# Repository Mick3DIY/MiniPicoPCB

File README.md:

<picture>
    
</picture>

# MiniPicoPCB

A simple PCB for the Raspberry Pi Pico with screw terminal headers (GPIOs, +3.3V, GND) to experiment with students.

## Printed Circuit Board (PCB) :

As part of an educational project, the schematic and PCB are made with [KiCad](https://www.kicad.org) version 9 ([kicad](kicad/) folder).

:bulb: All important parameters are stored in the schematic/PCB editors **text variables** (common project variables).

## Schematic :

## Printed Circuit Board (PCB) :

## PCB 3D view :

Thanks to [AISLER](https://aisler.net) PCB manufacturer :eu:

Get a unique 10€ coupon code in <ins>your first order</ins> in [AISLER](https://aisler.net) with my referral code : `MakeInEurope-ECYPW` :heart:

Thanks to "Jimmi Henry" for his 3D libraries (including this PCB Terminal Blocks)  in [GRABCAD Community](https://grabcad.com/jimmi.henry-1) in the [kicad/imports](kicad/imports) folder. 

## Bill Of Materials (BOM) :

| Ref  | Qty | Value | Footprint | Description |
| :---: | :---: | :--- | :--- | :--- |
| J1 ⟶ J10  | 10  | Screw_Terminal_01x05 | TerminalBlock_TE-Connectivity:TerminalBlock_TE_282834-5_1x05_P2.54mm_Horizontal | ... |
| J11, J12  | 2  | Conn_01x20_Socket | Connector_PinSocket_2.54mm:PinSocket_1x20_P2.54mm_Vertical | ... |

## TODO :

- [x] Add PDF files for the schematic and PCB
- [x] Add KiCad step file for the enclosure
- [ ] Add more files and examples, any ideas ? :laughing:

## Documentation :

Raspberry Pi Pico : https://www.raspberrypi.com/products/raspberry-pi-pico/

TE PCB terminal blocks : https://www.te.com/en/product-282834-5.html

> [!NOTE]
> Big thanks to the [KiCad](https://www.kicad.org) and plugins communities. :heart:

Happy soldering, coding & have fun ! :partying_face:

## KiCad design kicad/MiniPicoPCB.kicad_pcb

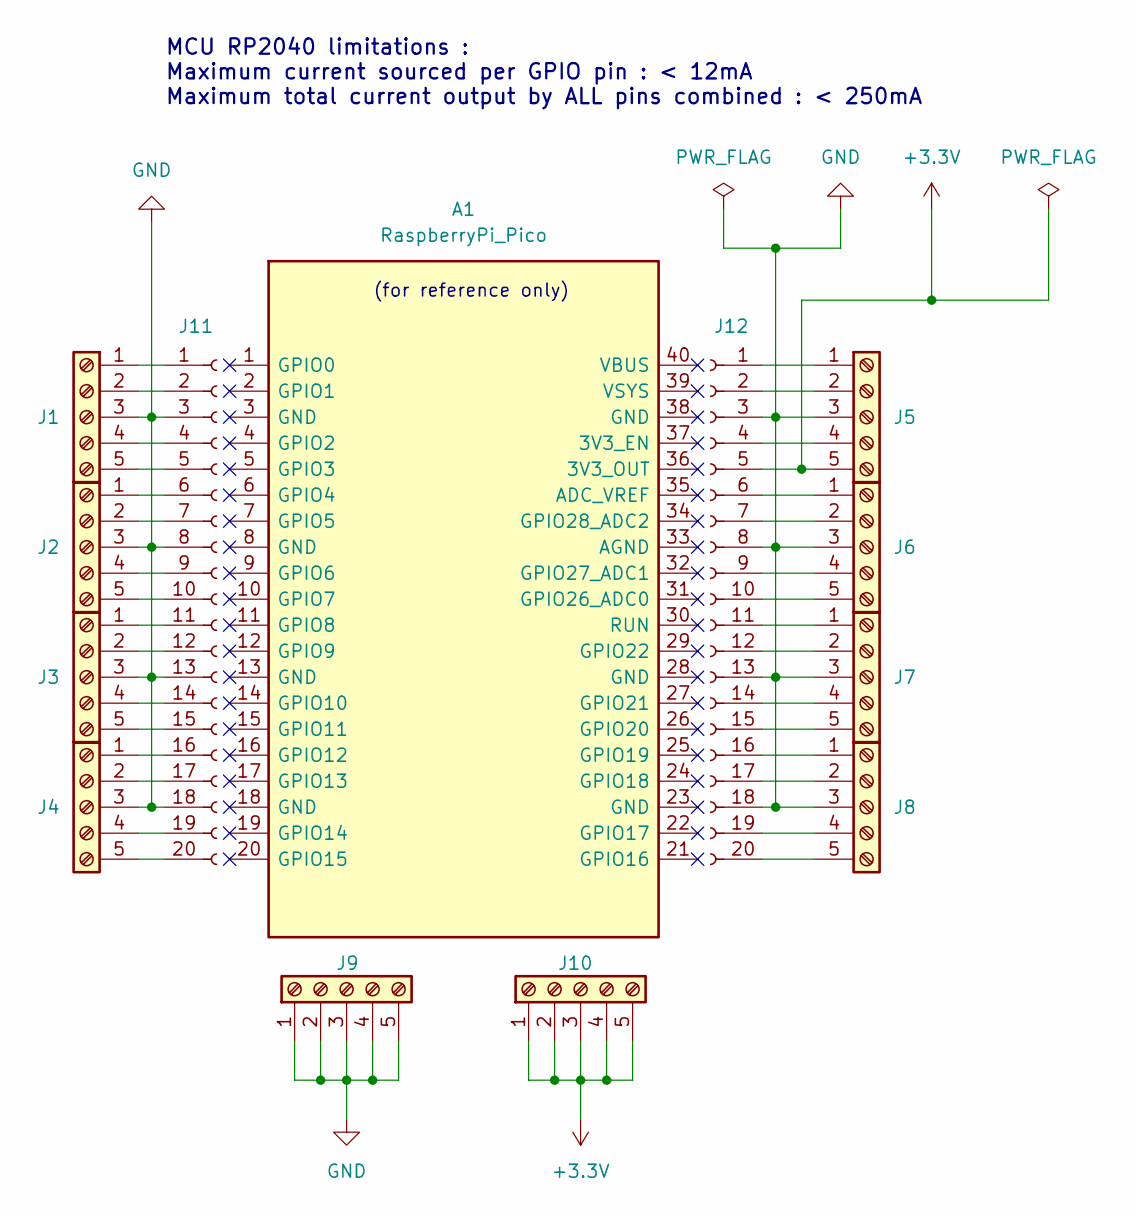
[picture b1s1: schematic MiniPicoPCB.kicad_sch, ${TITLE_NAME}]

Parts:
A1: RaspberryPi_Pico; RaspberryPi_Pico_Common_Unspecified
J1, J2, J3, J4, J5, J6, J7, J8, J9, J10: Screw_Terminal_01x05; TerminalBlock_TE_282834-5_1x05_P2.54mm_Horizontal
J11, J12: Conn_01x20_Socket; PinSocket_1x20_P2.54mm_Vertical

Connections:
+3.3V: J5.5, J10.1, J10.2, J10.3, J10.4, J10.5, J12.5
GND: J1.3, J2.3, J3.3, J4.3, J5.3, J6.3, J7.3, J8.3, J9.1, J9.2, J9.3, J9.4, J9.5, J11.3, J11.8, J11.13, J11.18, J12.3, J12.8, J12.13, J12.18
unnamed: J1.1, J11.1
unnamed: J1.2, J11.2
unnamed: J1.4, J11.4
unnamed: J1.5, J11.5
unnamed: J2.1, J11.6
unnamed: J2.2, J11.7
unnamed: J2.4, J11.9
unnamed: J2.5, J11.10
unnamed: J3.1, J11.11
unnamed: J3.2, J11.12
unnamed: J3.4, J11.14
unnamed: J3.5, J11.15
unnamed: J4.1, J11.16
unnamed: J4.2, J11.17
unnamed: J4.4, J11.19
unnamed: J4.5, J11.20
unnamed: J5.1, J12.1
unnamed: J5.2, J12.2
unnamed: J5.4, J12.4
unnamed: J6.1, J12.6
unnamed: J6.2, J12.7
unnamed: J6.4, J12.9
unnamed: J6.5, J12.10
unnamed: J7.1, J12.11
unnamed: J7.2, J12.12
unnamed: J7.4, J12.14
unnamed: J7.5, J12.15
unnamed: J8.1, J12.16
unnamed: J8.2, J12.17
unnamed: J8.4, J12.19
unnamed: J8.5, J12.20

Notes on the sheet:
MCU RP2040 limitations : Maximum current sourced per GPIO pin : < 12mA Maximum total current output by ALL pins combined : < 250mA
(for reference only)

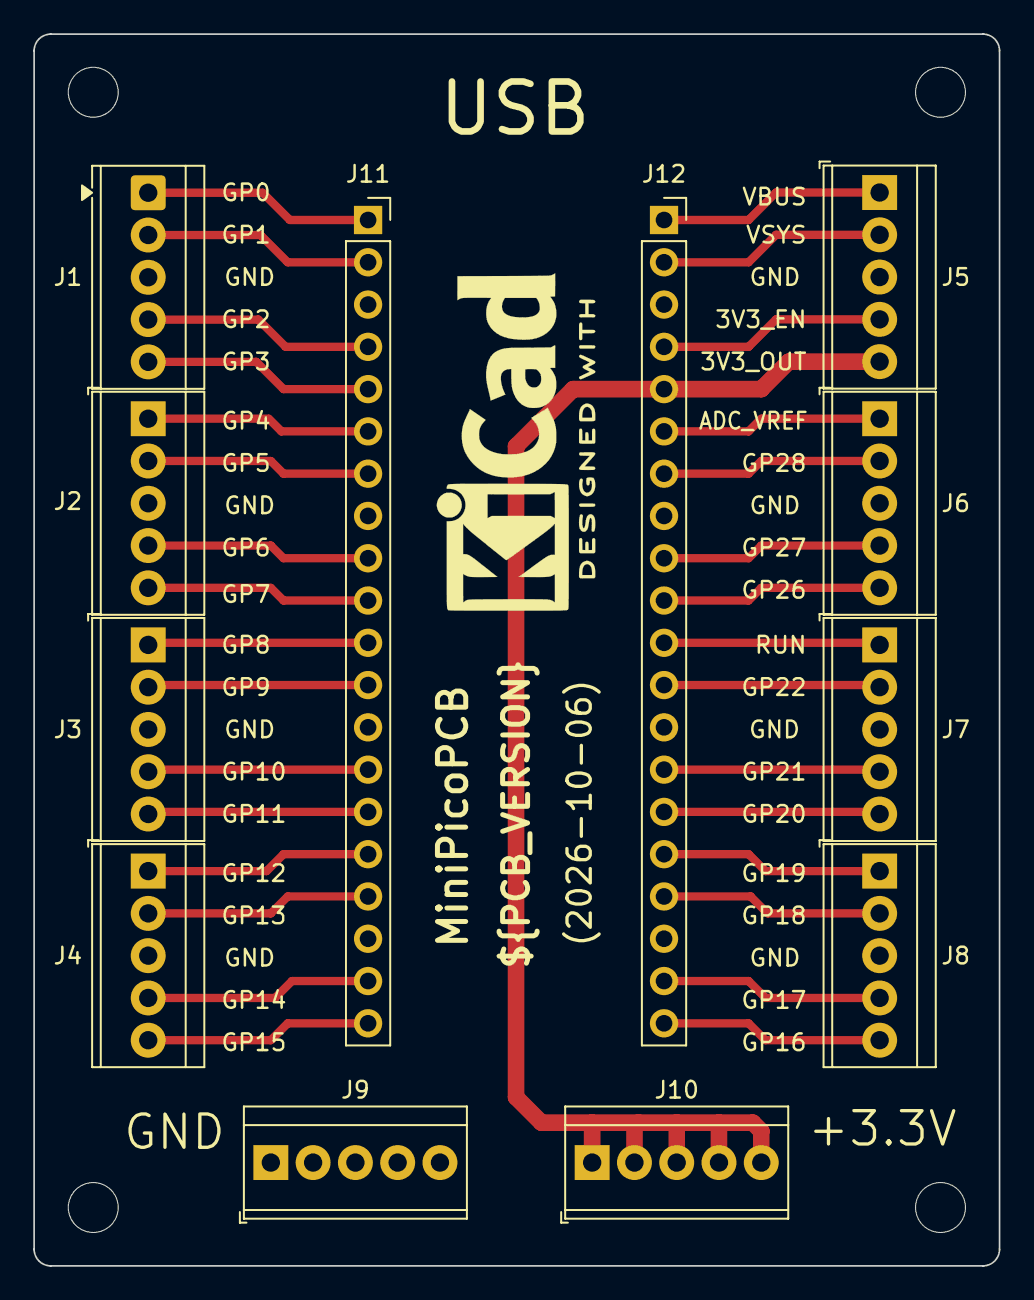
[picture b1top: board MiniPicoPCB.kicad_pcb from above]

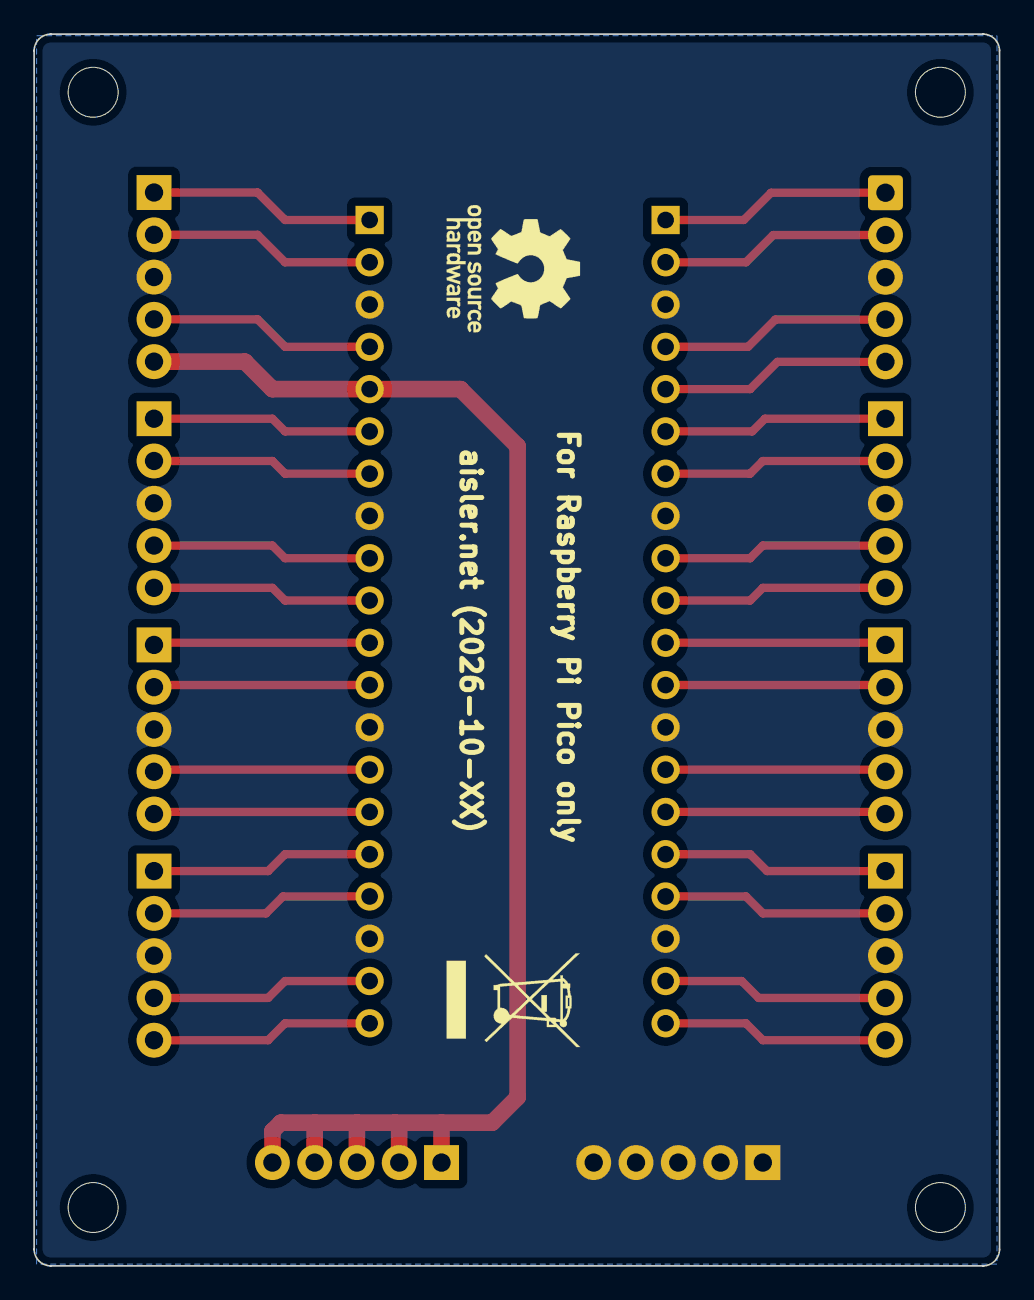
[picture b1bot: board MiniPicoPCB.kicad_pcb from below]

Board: 2 copper layers, 58.0 x 74.0 mm, 15 parts (2 on the bottom side), 33 nets.

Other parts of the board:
LogoKicad8: KiCad-Logo2_8mm_SilkScreen
REFOSW: OSHW-Logo_7.5x8mm_SilkScreen
REFTRASH: WEEE-Logo_5.6x8mm_SilkScreen
